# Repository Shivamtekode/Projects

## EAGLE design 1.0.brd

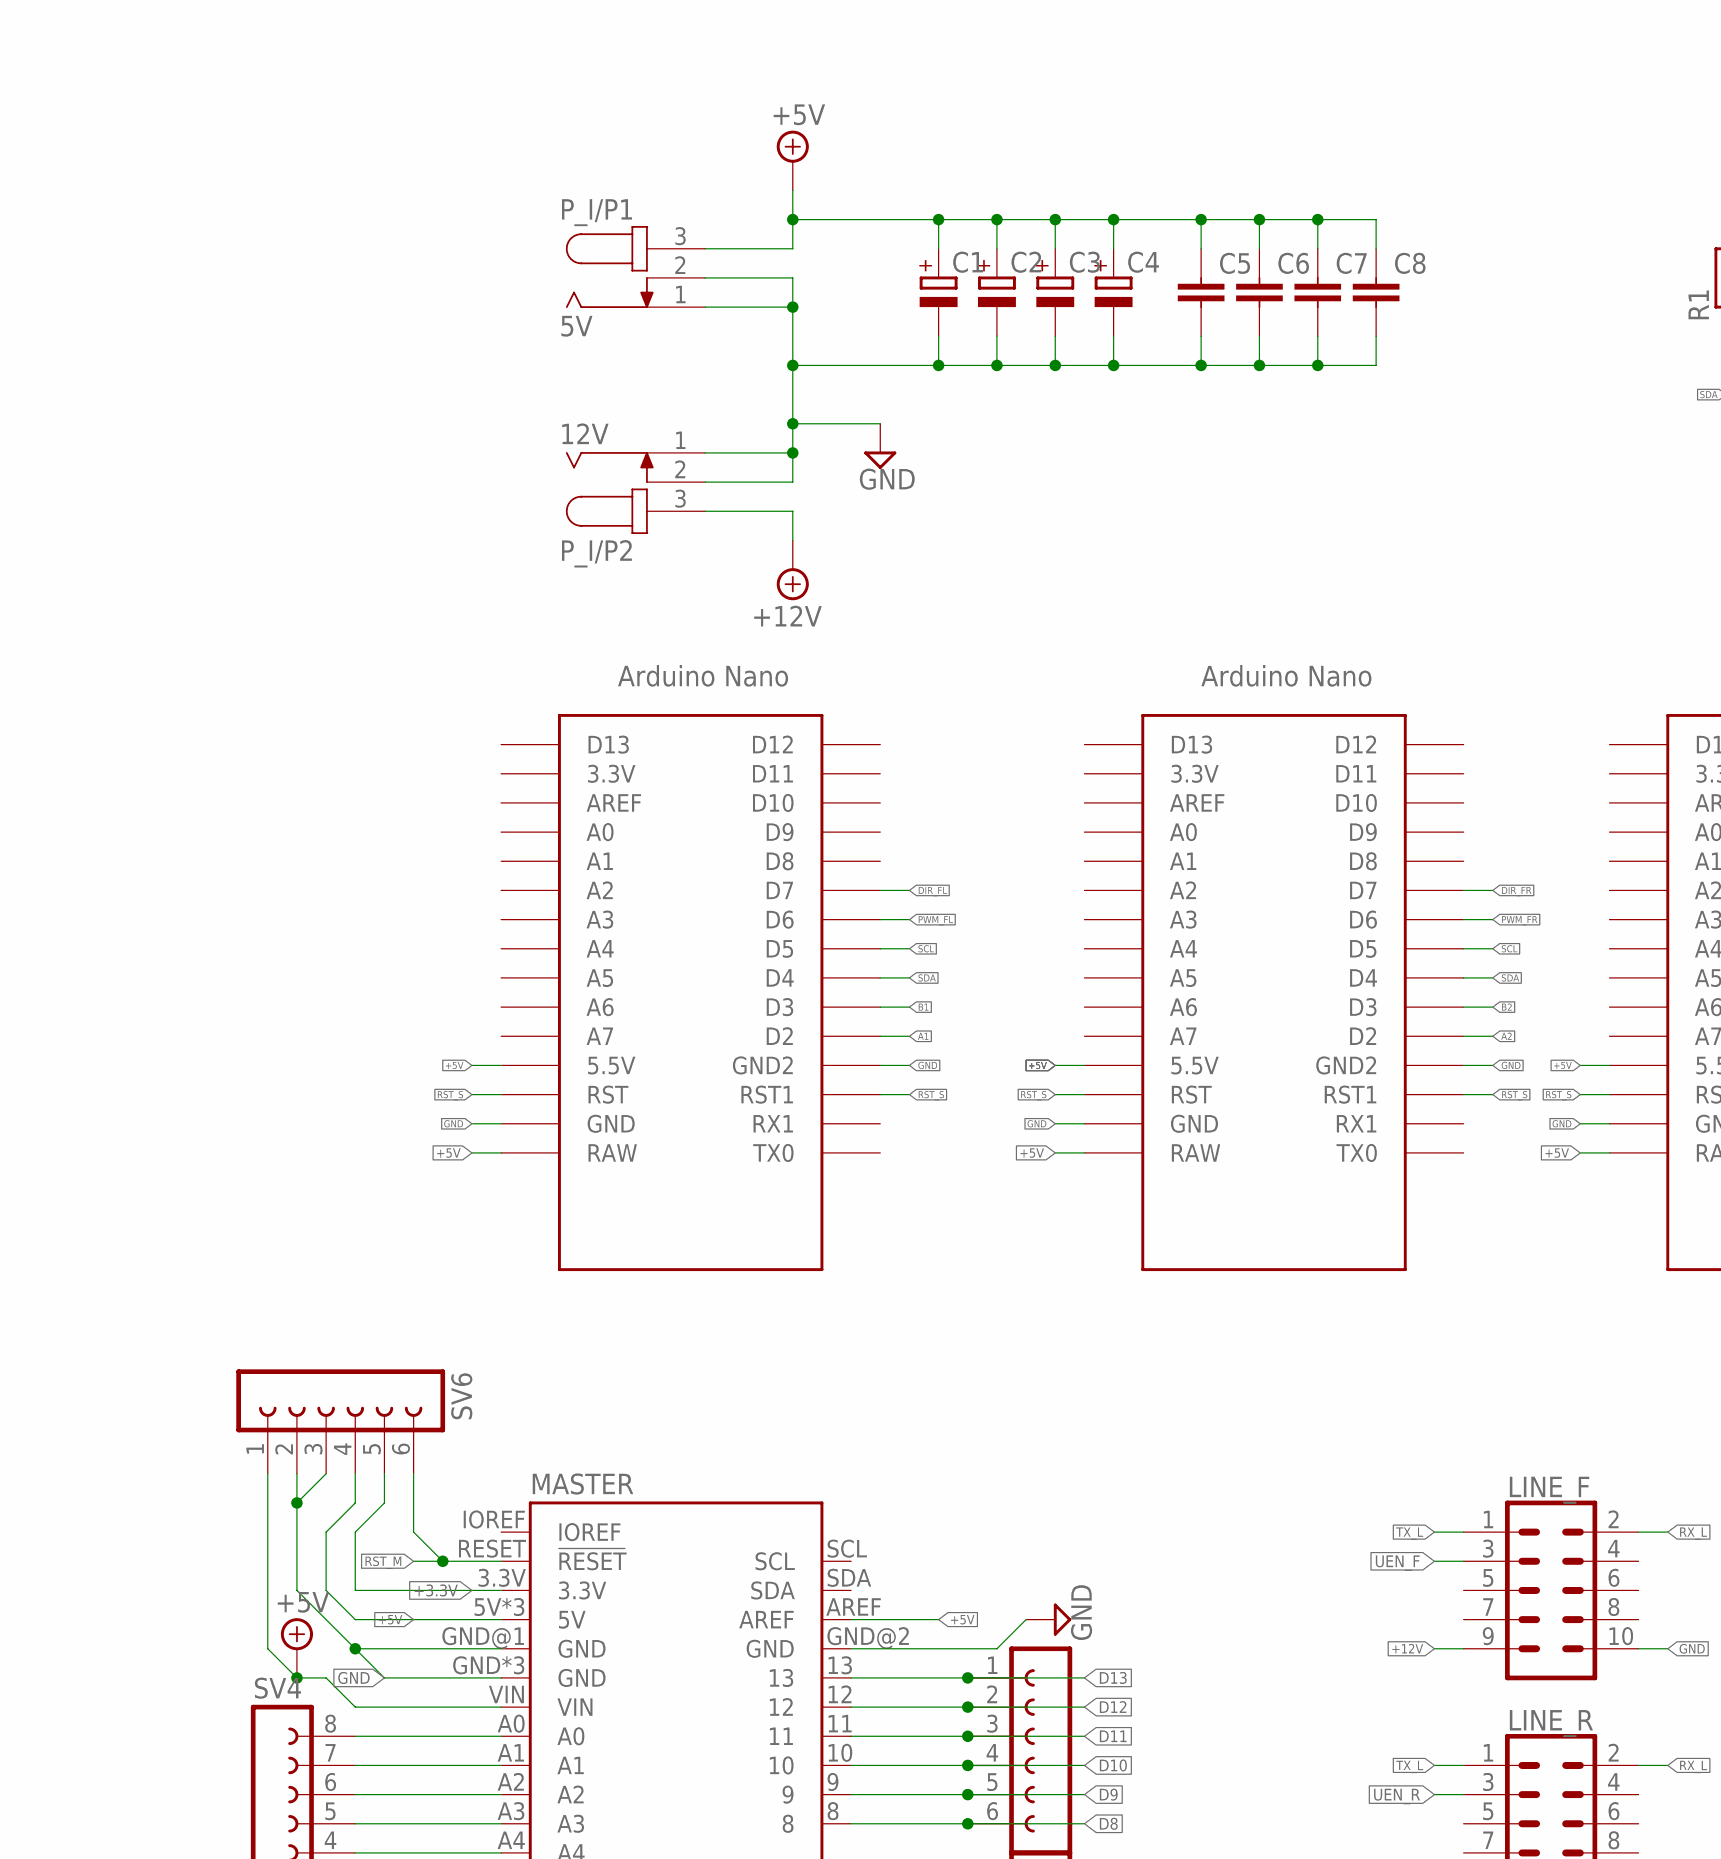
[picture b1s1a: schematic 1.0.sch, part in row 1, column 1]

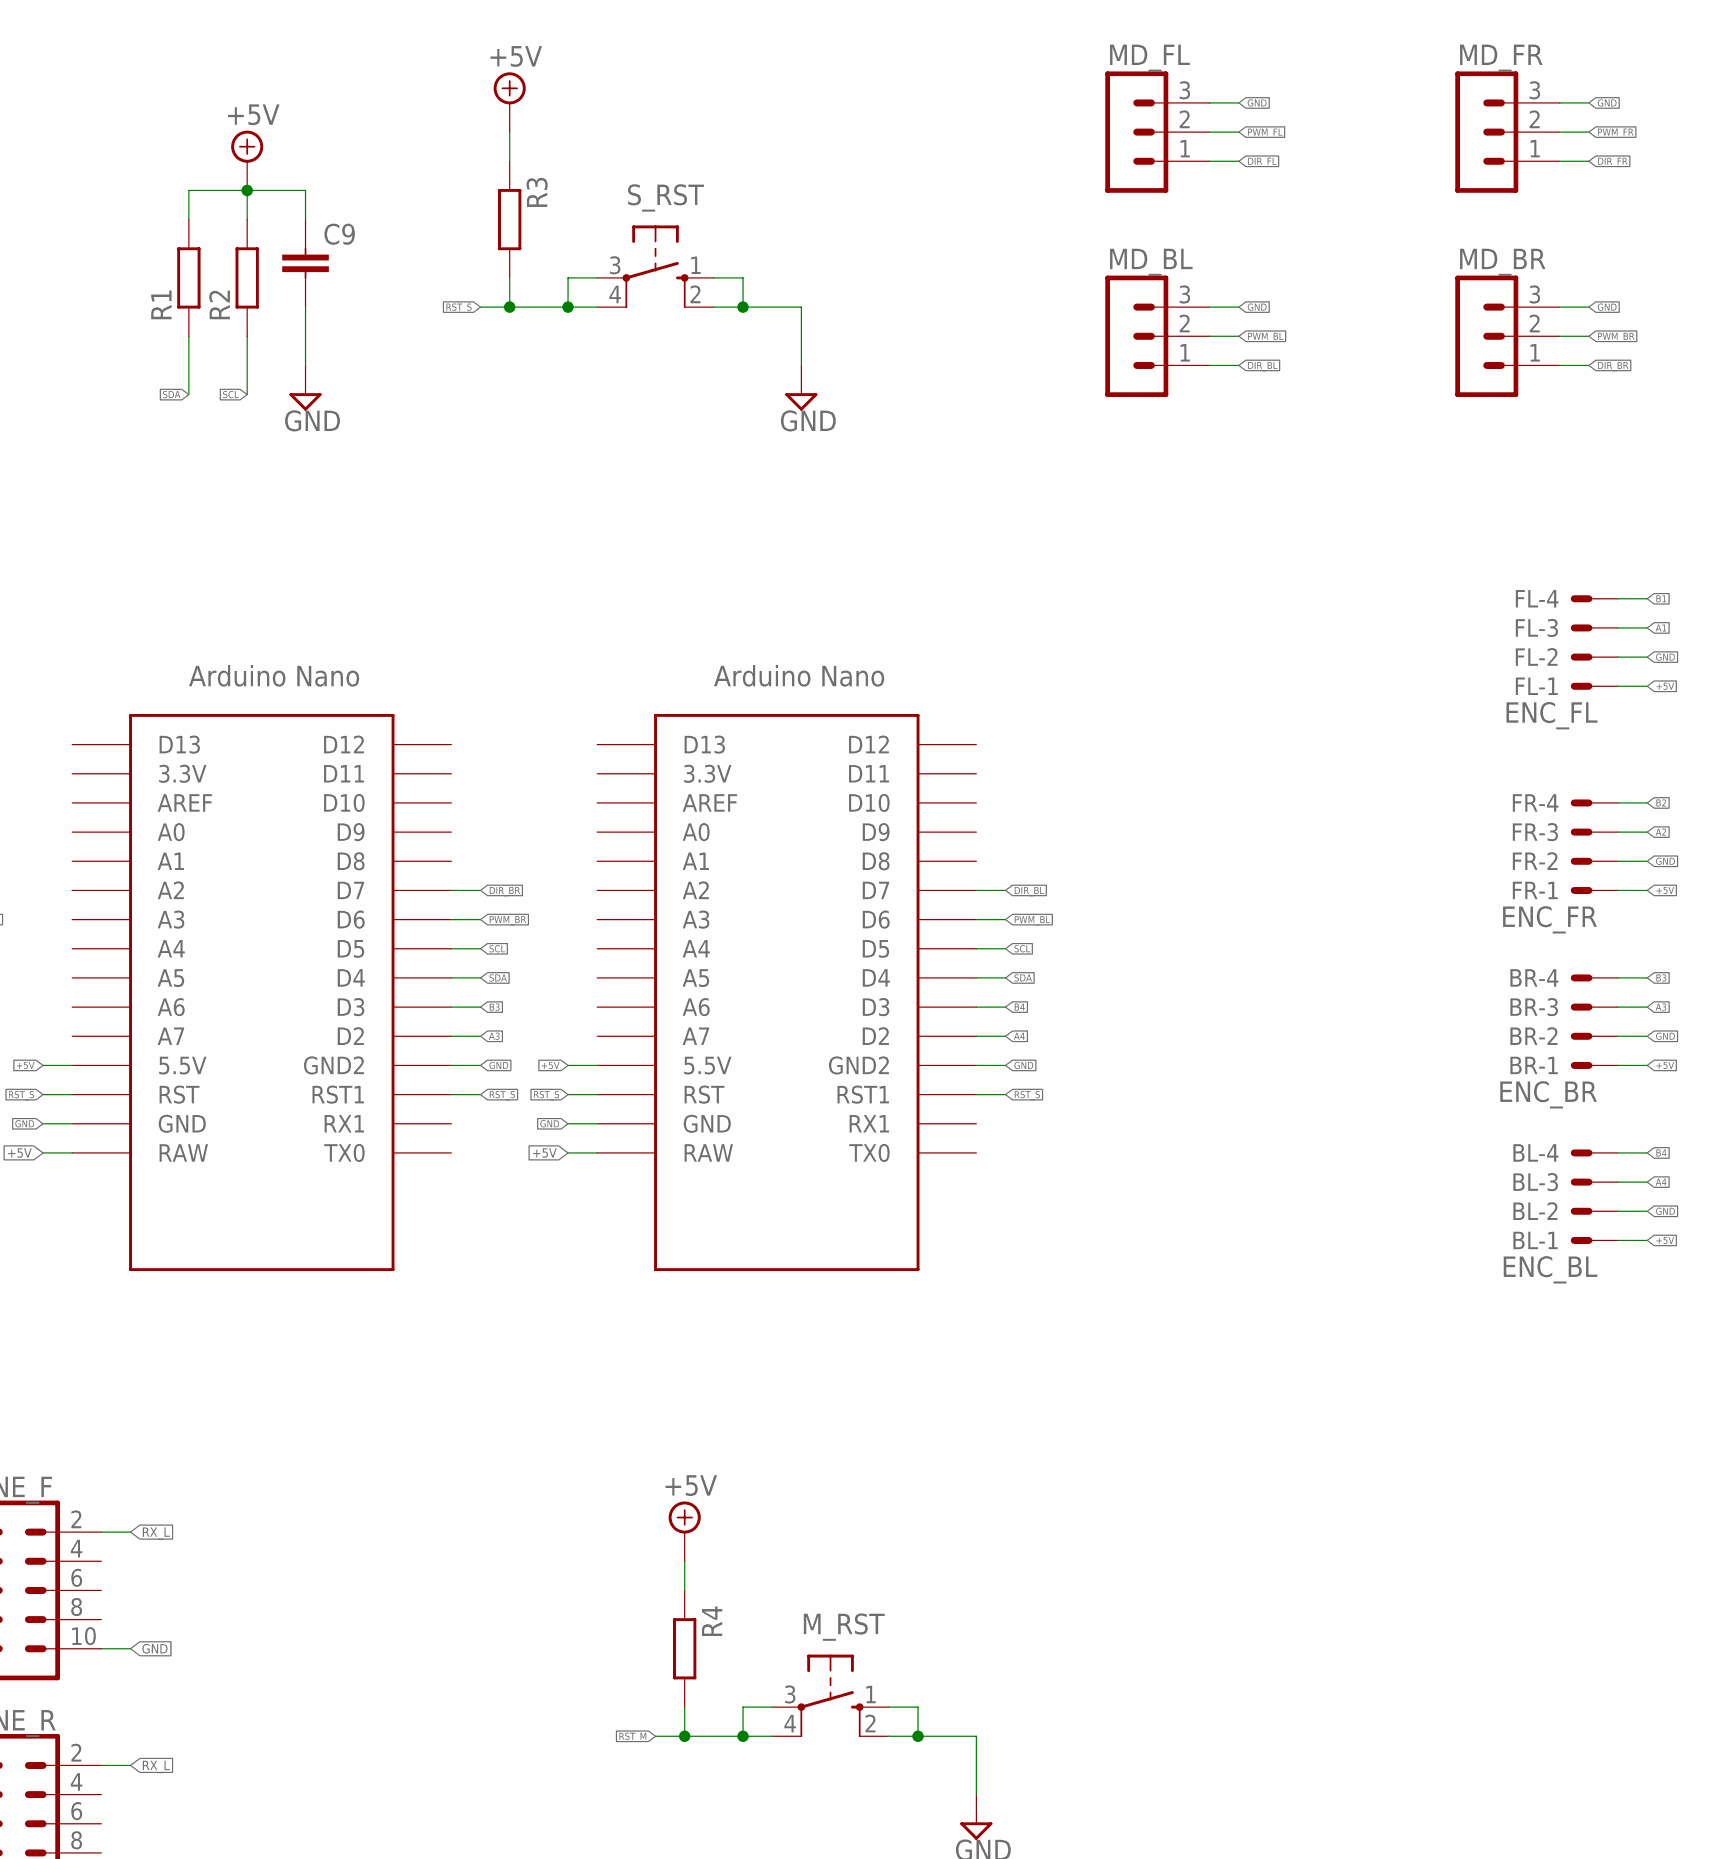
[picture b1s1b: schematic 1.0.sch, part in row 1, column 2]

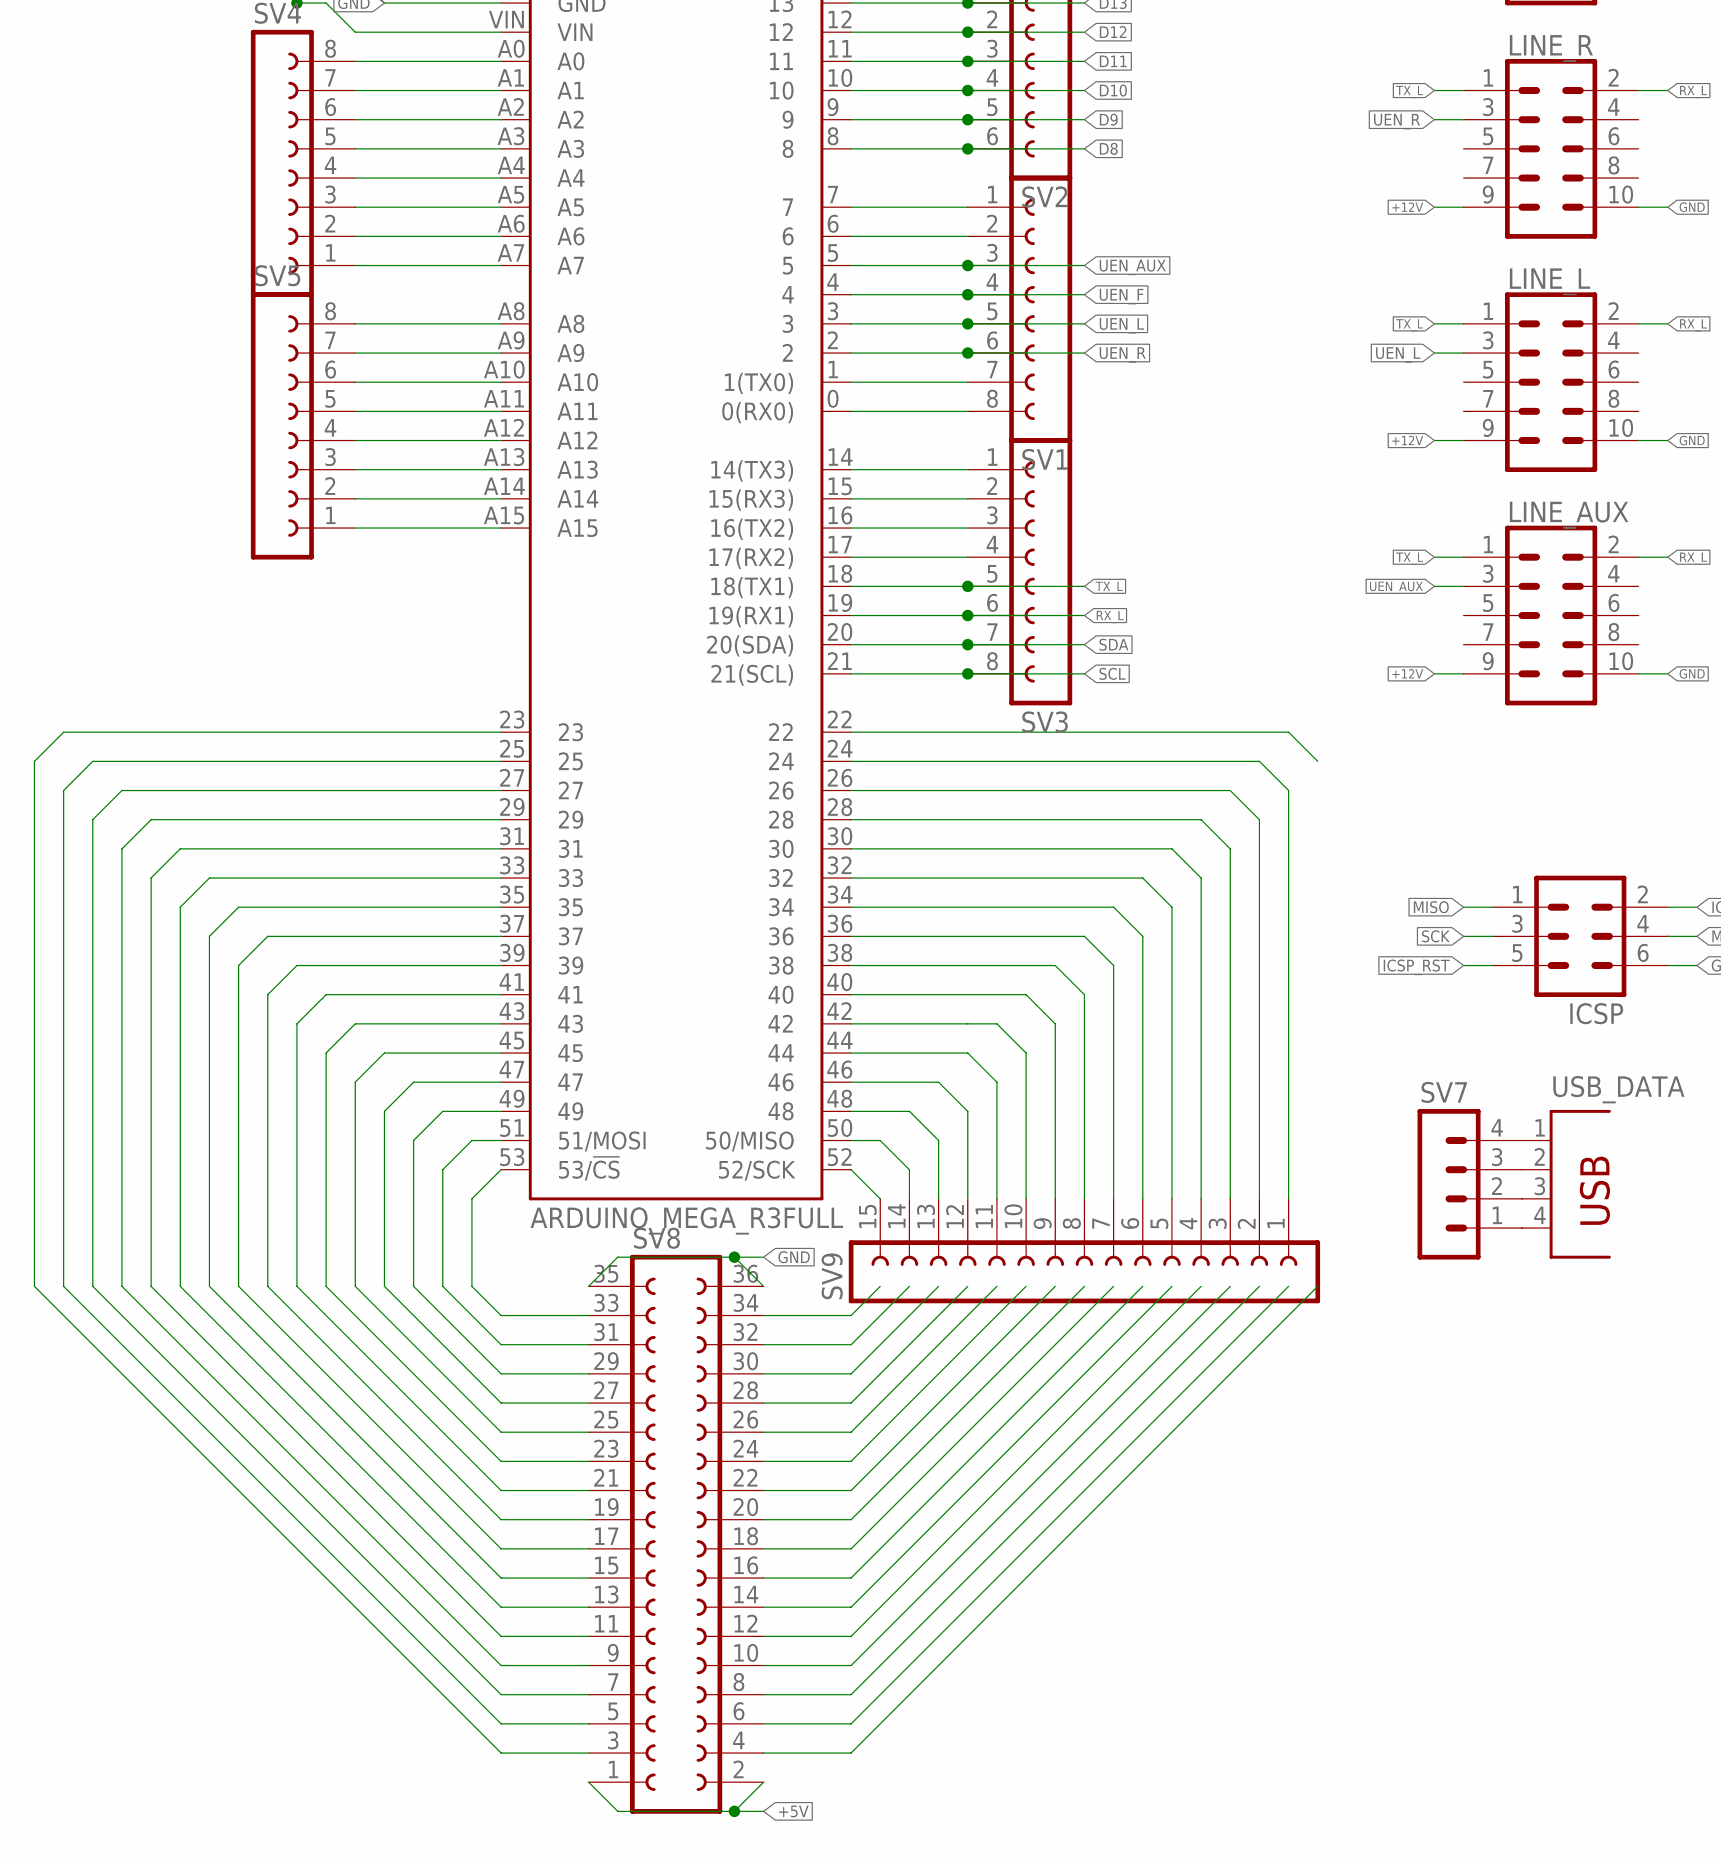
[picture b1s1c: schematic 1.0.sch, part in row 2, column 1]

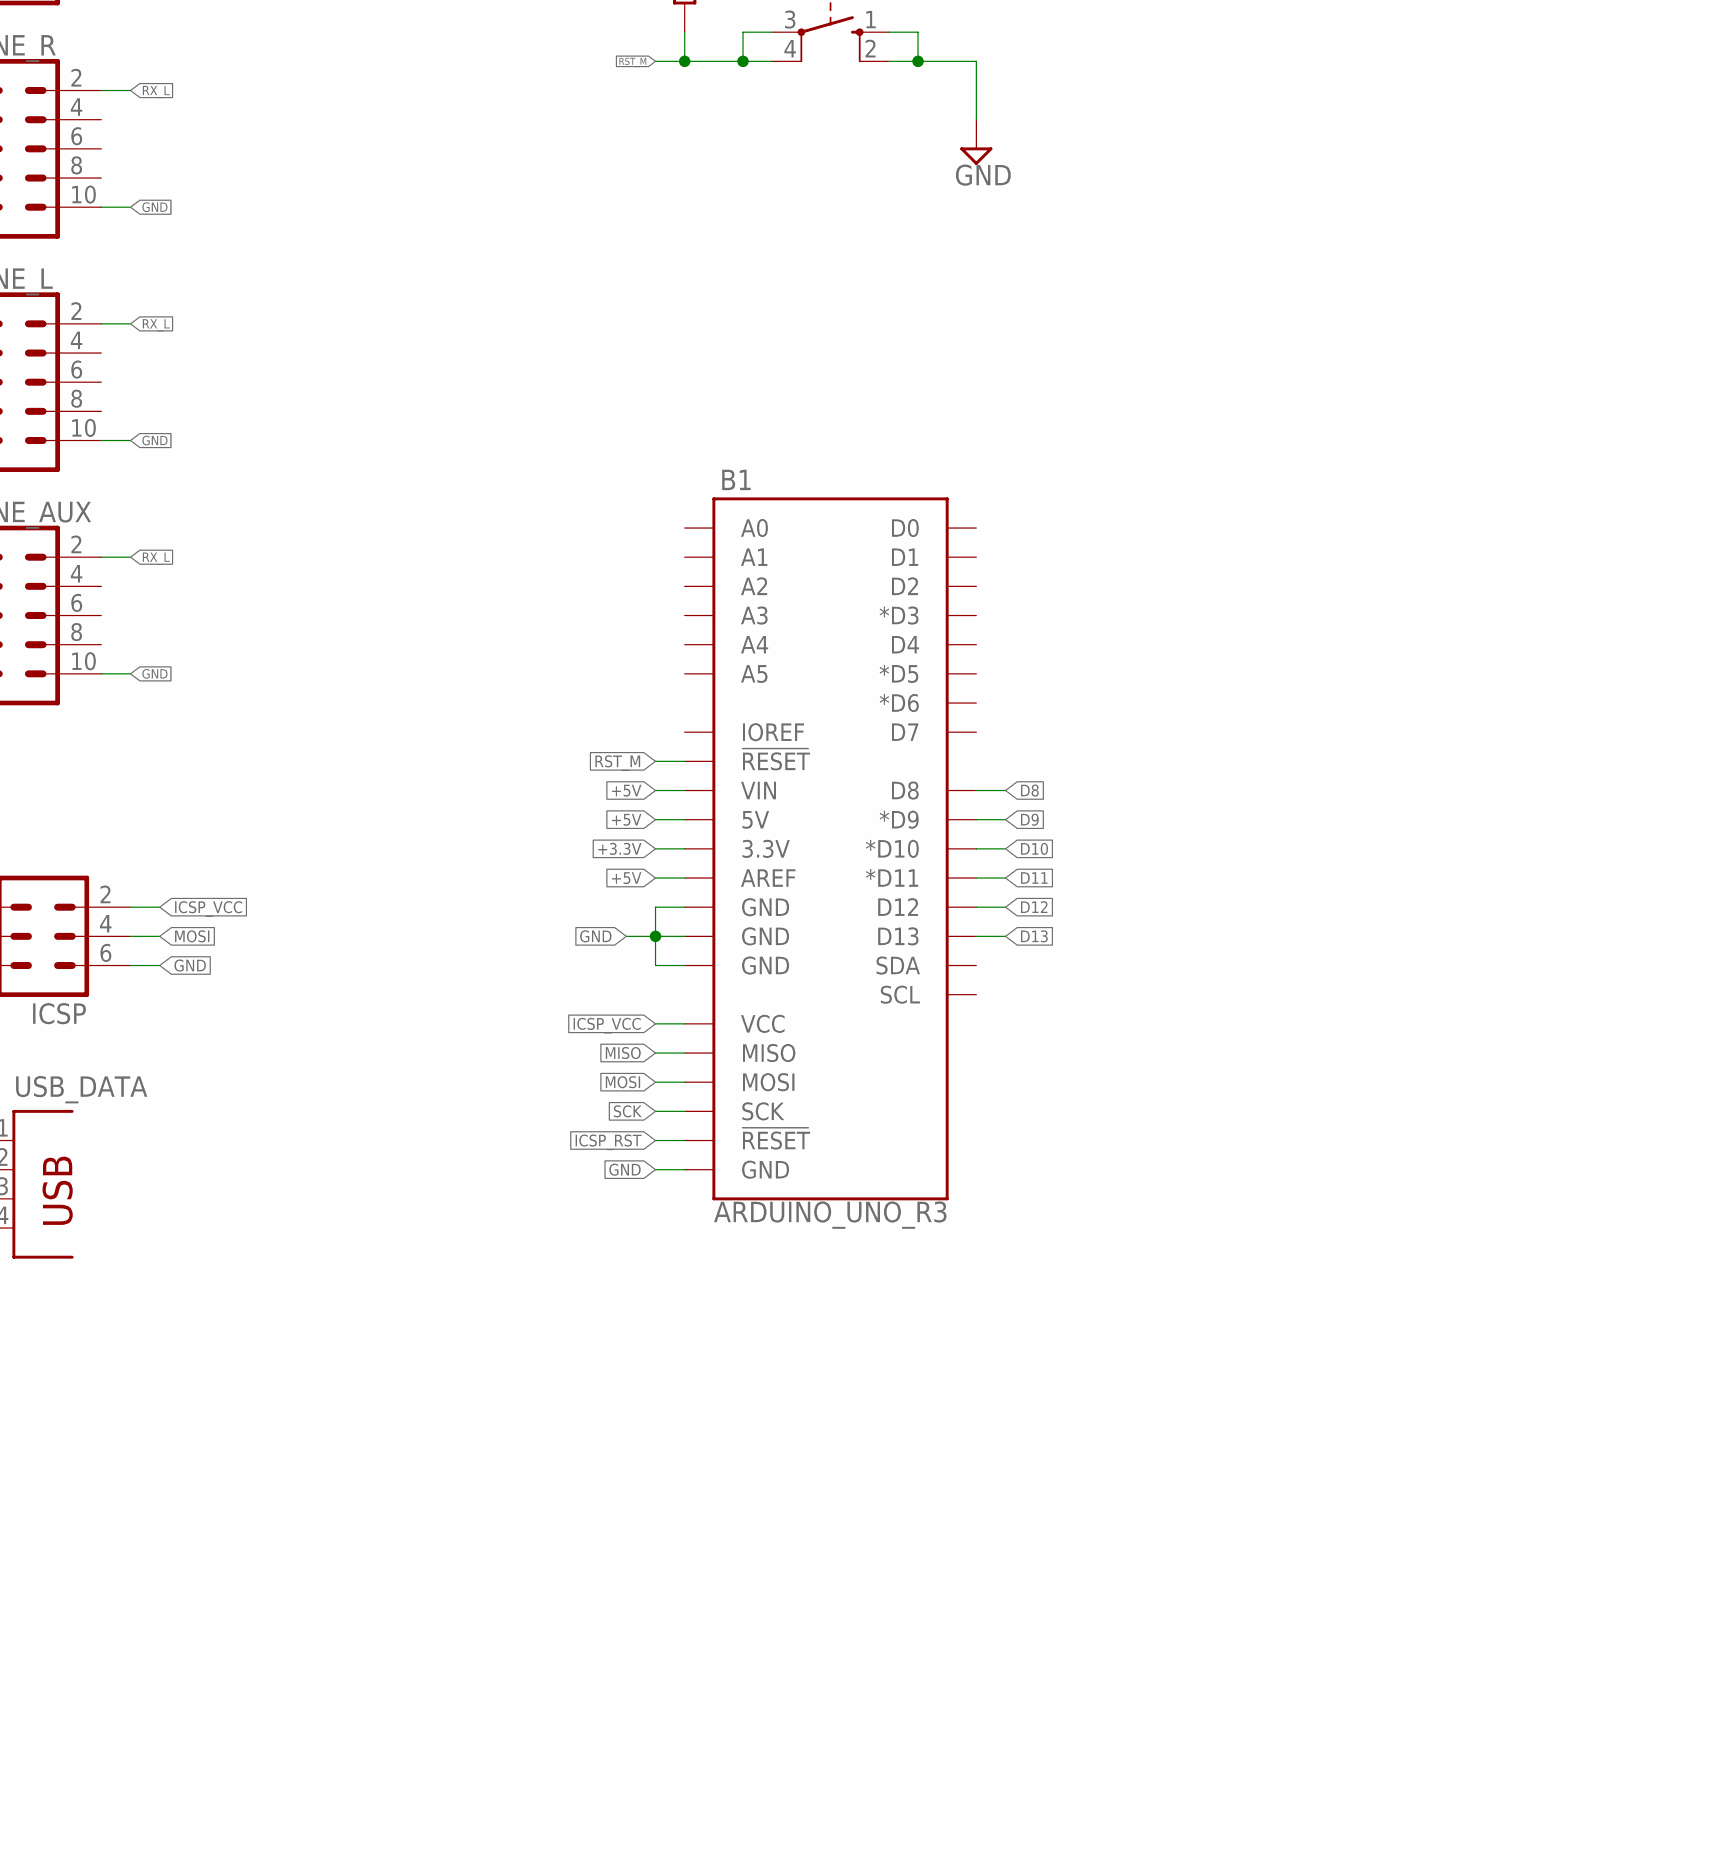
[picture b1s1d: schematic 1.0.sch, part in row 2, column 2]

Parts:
B1: ARDUINO_UNO_R3; ARDUINO_R3
BL: ENC_BL; 22-23-2041
BR: ENC_BR; 22-23-2041
C1, C2, C3, C4: CPOL-EUE5-10.5; E5-10,5
C5, C6, C7, C8, C9: C-EU050-035X075; C050-035X075
FL: ENC_FL; 22-23-2041
FR: ENC_FR; 22-23-2041
ICSP: MA03-2
LINE_AUX: CONN_05X2SHD_LOCK; 2X5-SHROUDED_LOCK
LINE_F: CONN_05X2SHD_LOCK; 2X5-SHROUDED_LOCK
LINE_L: CONN_05X2SHD_LOCK; 2X5-SHROUDED_LOCK
LINE_R: CONN_05X2SHD_LOCK; 2X5-SHROUDED_LOCK
MASTER: ARDUINO_MEGA_R3FULL; ARDUINO_MEGA_NO_SILK
MD_BL: MA03-1
MD_BR: MA03-1
MD_FL: MA03-1
MD_FR: MA03-1
M_RST: 10-XX; B3F-10XX
P_I/P1: 5V; SPC4078
P_I/P2: 12V; SPC4078
R1, R2, R3, R4: R-EU_0207/10; 0207/10
SLAVE_0: NANO_08; NANO
SLAVE_1: NANO_09; NANO
SLAVE_2: NANO_11; NANO
SLAVE_3: NANO_10; NANO
SV1, SV3, SV4, SV5: FE08-1; FE08
SV2, SV6: FE06-1; FE06
SV7: MA04-1
SV8: FE18-2
SV9: FE15-1; FE15
S_RST: 10-XX; B3F-10XX
USB_DATA: PN61729

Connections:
+3.3V: B1.3.3V, MASTER.3.3V, SV6.5
+5V: B1.5V, B1.AREF, B1.VIN, BL.1, BR.1, C1.+, C2.+, C3.+, C4.+, C5.1, C6.1, C7.1, C8.1, C9.1, FL.1, FR.1, MASTER.5V, MASTER.5V@1 (5V), MASTER.5V@2 (5V), MASTER.AREF, MASTER.VIN, P_I/P1.3, R1.2, R2.2, R3.1, R4.1, SLAVE_0.5V (5.5V), SLAVE_0.RAW, SLAVE_1.5V (5.5V), SLAVE_1.RAW, SLAVE_2.5V (5.5V), SLAVE_2.RAW, SLAVE_3.5V (5.5V), SLAVE_3.RAW, SV6.1, SV6.4, SV8.1, SV8.2
+12V: LINE_AUX.9, LINE_F.9, LINE_L.9, LINE_R.9, P_I/P2.3
A1: FL.3, SLAVE_0.D2
A2: FR.3, SLAVE_1.D2
A3: BR.3, SLAVE_2.D2
A4: BL.3, SLAVE_3.D2
B1: FL.4, SLAVE_0.D3
B2: FR.4, SLAVE_1.D3
B3: BR.4, SLAVE_2.D3
B4: BL.4, SLAVE_3.D3
D8: B1.D8, MASTER.8, SV2.6
D9: B1.D9 (*D9), MASTER.9, SV2.5
D10: B1.D10 (*D10), MASTER.10, SV2.4
D11: B1.D11 (*D11), MASTER.11, SV2.3
D12: B1.D12, MASTER.12, SV2.2
D13: B1.D13, MASTER.13, SV2.1
DIR_BL: MD_BL.1, SLAVE_3.D7
DIR_BR: MD_BR.1, SLAVE_2.D7
DIR_FL: MD_FL.1, SLAVE_0.D7
DIR_FR: MD_FR.1, SLAVE_1.D7
GND: B1.GND@1 (GND), B1.GND@2 (GND), B1.GND@4 (GND), BL.2, BR.2, C1.-, C2.-, C3.-, C4.-, C5.2, C6.2, C7.2, C8.2, C9.2, FL.2, FR.2, ICSP.6, LINE_AUX.10, LINE_F.10, LINE_L.10, LINE_R.10, MASTER.GND, MASTER.GND@1 (GND), MASTER.GND@2 (GND), MASTER.GND@3 (GND), MASTER.GND@4 (GND), MD_BL.3, MD_BR.3, MD_FL.3, MD_FR.3, M_RST.1 (S), M_RST.2 (S1), P_I/P1.1, P_I/P1.2, P_I/P2.1, P_I/P2.2, SLAVE_0.GND, SLAVE_0.GND1 (GND2), SLAVE_1.GND, SLAVE_1.GND1 (GND2), SLAVE_2.GND, SLAVE_2.GND1 (GND2), SLAVE_3.GND, SLAVE_3.GND1 (GND2), SV6.2, SV6.3, SV8.35, SV8.36, S_RST.1 (S), S_RST.2 (S1)
ICSP_RST: B1.RESET@2 (!RESET!), ICSP.5
ICSP_VCC: B1.VCC, ICSP.2
MISO: B1.MISO, ICSP.1
MOSI: B1.MOSI, ICSP.4
unnamed: MASTER.14 (14(TX3)), SV3.1
unnamed: SV7.1, USB_DATA.4
unnamed: SV7.2, USB_DATA.3
unnamed: SV7.3, USB_DATA.2
unnamed: SV7.4, USB_DATA.1
unnamed: MASTER.24, SV9.1
unnamed: MASTER.0 (0(RX0)), SV1.8
unnamed: MASTER.1 (1(TX0)), SV1.7
unnamed: MASTER.15 (15(RX3)), SV3.2
unnamed: MASTER.16 (16(TX2)), SV3.3
unnamed: MASTER.17 (17(RX2)), SV3.4
unnamed: MASTER.53 (53/!CS), SV8.33
unnamed: MASTER.6, SV1.2
unnamed: MASTER.7, SV1.1
unnamed: MASTER.51 (51/MOSI), SV8.31
unnamed: MASTER.26, SV9.2
unnamed: MASTER.47, SV8.27
unnamed: MASTER.49, SV8.29
unnamed: MASTER.45, SV8.25
unnamed: MASTER.43, SV8.23
unnamed: MASTER.41, SV8.21
unnamed: MASTER.39, SV8.19
unnamed: MASTER.A0, SV4.8
unnamed: MASTER.A1, SV4.7
unnamed: MASTER.A2, SV4.6
unnamed: MASTER.A3, SV4.5
unnamed: MASTER.A4, SV4.4
unnamed: MASTER.A5, SV4.3
unnamed: MASTER.A6, SV4.2
unnamed: MASTER.A7, SV4.1
unnamed: MASTER.A8, SV5.8
unnamed: MASTER.A9, SV5.7
unnamed: MASTER.A10, SV5.6
unnamed: MASTER.A11, SV5.5
unnamed: MASTER.A12, SV5.4
unnamed: MASTER.A13, SV5.3
unnamed: MASTER.A14, SV5.2
unnamed: MASTER.A15, SV5.1
unnamed: MASTER.37, SV8.17
unnamed: MASTER.35, SV8.15
unnamed: MASTER.33, SV8.13
unnamed: MASTER.31, SV8.11
unnamed: MASTER.29, SV8.9
unnamed: MASTER.27, SV8.7
unnamed: MASTER.25, SV8.5
unnamed: MASTER.23, SV8.3
unnamed: MASTER.28, SV9.3
unnamed: MASTER.30, SV9.4
unnamed: MASTER.32, SV9.5
unnamed: MASTER.34, SV9.6
unnamed: MASTER.36, SV9.7
unnamed: MASTER.38, SV9.8
unnamed: MASTER.40, SV9.9
unnamed: MASTER.42, SV9.10
unnamed: MASTER.52 (52/SCK), SV9.15
unnamed: MASTER.50 (50/MISO), SV9.14
unnamed: MASTER.48, SV9.13
unnamed: MASTER.46, SV9.12
unnamed: MASTER.44, SV9.11
PWM_BL: MD_BL.2, SLAVE_3.D6
PWM_BR: MD_BR.2, SLAVE_2.D6
PWM_FL: MD_FL.2, SLAVE_0.D6
PWM_FR: MD_FR.2, SLAVE_1.D6
RST_M: B1.RESET@1 (!RESET!), MASTER.RESET (!RESET), M_RST.3, M_RST.4 (P1), R4.2, SV6.6
RST_S: R3.2, SLAVE_0.RST, SLAVE_0.RST1, SLAVE_1.RST, SLAVE_1.RST1, SLAVE_2.RST, SLAVE_2.RST1, SLAVE_3.RST, SLAVE_3.RST1, S_RST.3, S_RST.4 (P1)
RX_L: LINE_AUX.2, LINE_F.2, LINE_L.2, LINE_R.2, MASTER.19 (19(RX1)), SV3.6
SCK: B1.SCK, ICSP.3
SCL: MASTER.21 (21(SCL)), R2.1, SLAVE_0.D5, SLAVE_1.D5, SLAVE_2.D5, SLAVE_3.D5, SV3.8
SDA: MASTER.20 (20(SDA)), R1.1, SLAVE_0.D4, SLAVE_1.D4, SLAVE_2.D4, SLAVE_3.D4, SV3.7
TX_L: LINE_AUX.1, LINE_F.1, LINE_L.1, LINE_R.1, MASTER.18 (18(TX1)), SV3.5
UEN_AUX: LINE_AUX.3, MASTER.5, SV1.3
UEN_F: LINE_F.3, MASTER.4, SV1.4
UEN_L: LINE_L.3, MASTER.3, SV1.5
UEN_R: LINE_R.3, MASTER.2, SV1.6

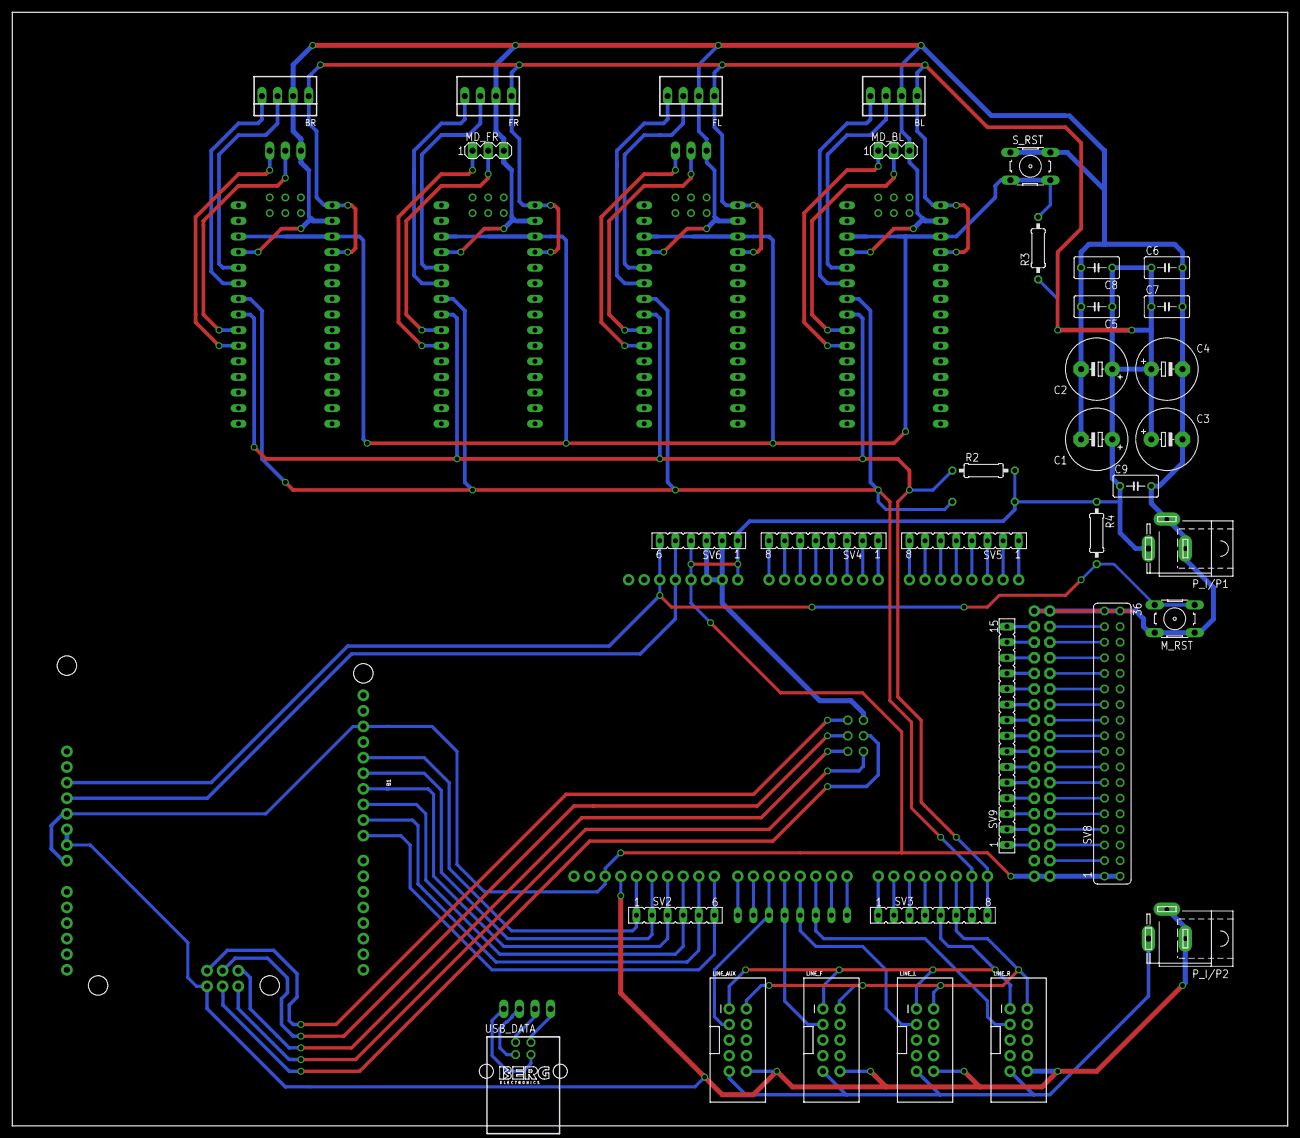
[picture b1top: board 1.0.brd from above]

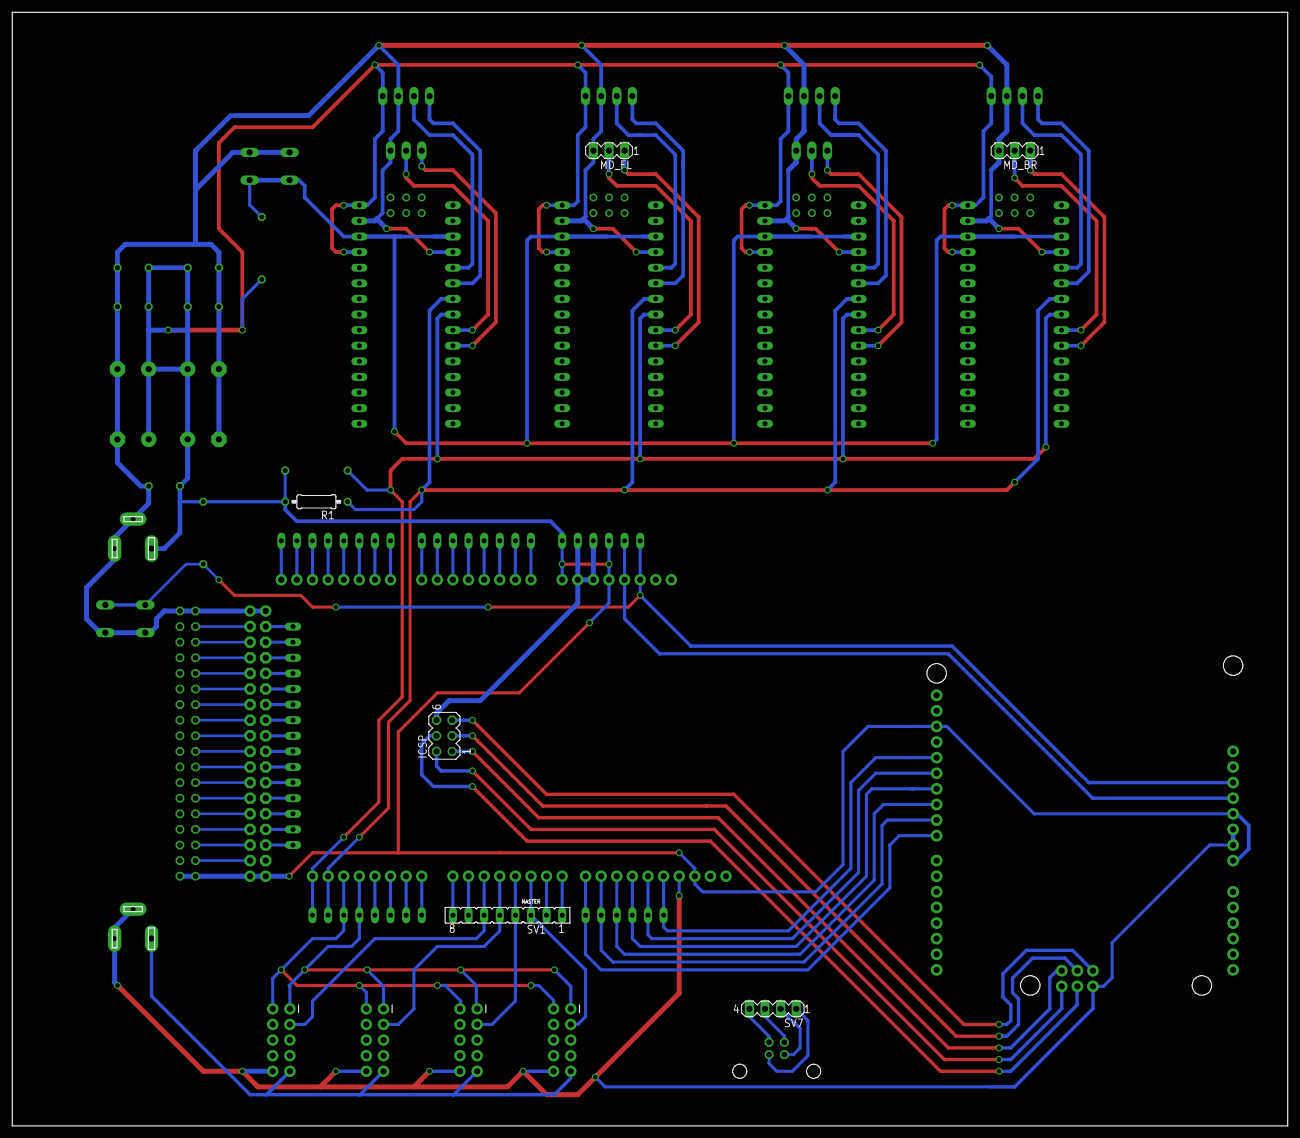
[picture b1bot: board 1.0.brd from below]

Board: 2 copper layers, 207.6 x 181.3 mm, 46 parts (7 on the bottom side), 100 nets.

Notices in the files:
parts and their libraries:
SparkFun-Boards: Licensing: Creative Commons ShareAlike 4.0 International - https://creativecommons.org/licenses/by-sa/4.0
